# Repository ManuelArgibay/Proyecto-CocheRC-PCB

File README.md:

# Proyecto MiSE — Custom PCB

View this project on [CADLAB.io](https://cadlab.io/project/30101).

PCB diseñada para la asignatura de Microcontroladores i Sistemes Empotrats (MiSE) de la Universitat de Barcelona. El diseño fue realizado íntegramente en KiCad, incluyendo esquemático, layout y exportación de Gerbers.

## Hardware

| Componente | Descripción |
|---|---|
| MSP430FR2355TPT | Microcontrolador TI MSP430, 48-pin QFP, bajo consumo |
| LMV324 | Amplificador operacional cuádruple (acondicionamiento de señal) |
| THB001P | Switch codificador (C&K Components, 14 pines) |
| LCD 2×16 I2C | Display alfanumérico con interfaz I2C (Midas) |
| LDR | Fotorresistencia para detección de luz |
| WIFI | Módulo de conectividad inalámbrica |
| Crystal | Oscilador de cristal externo |
| Pasivos SMD | Resistencias y condensadores en encapsulado 0805 |

## Estructura del repositorio
├── PCB_MiSE.kicad_pcb       # Layout de la PCB
├── PCB_MiSE.kicad_sch       # Esquemático
├── PCB_MiSE.kicad_pro       # Archivo de proyecto KiCad
├── Gerbers/                  # Archivos de fabricación
├── Componentes/
│   └── MiSE.pretty/         # Librería de footprints personalizada
└── PCB_MiSE-backups/        # Backups automáticos de KiCad

## Fabricación

Los archivos Gerber listos para enviar a fabricar están en la carpeta `Gerbers/`. El diseño es una PCB de 2 capas con componentes SMD (0805) y through-hole.

## Herramientas

- [KiCad](https://www.kicad.org/) 8.x
- [CADLAB.io](https://cadlab.io) — revisión visual de cambios en el PCB

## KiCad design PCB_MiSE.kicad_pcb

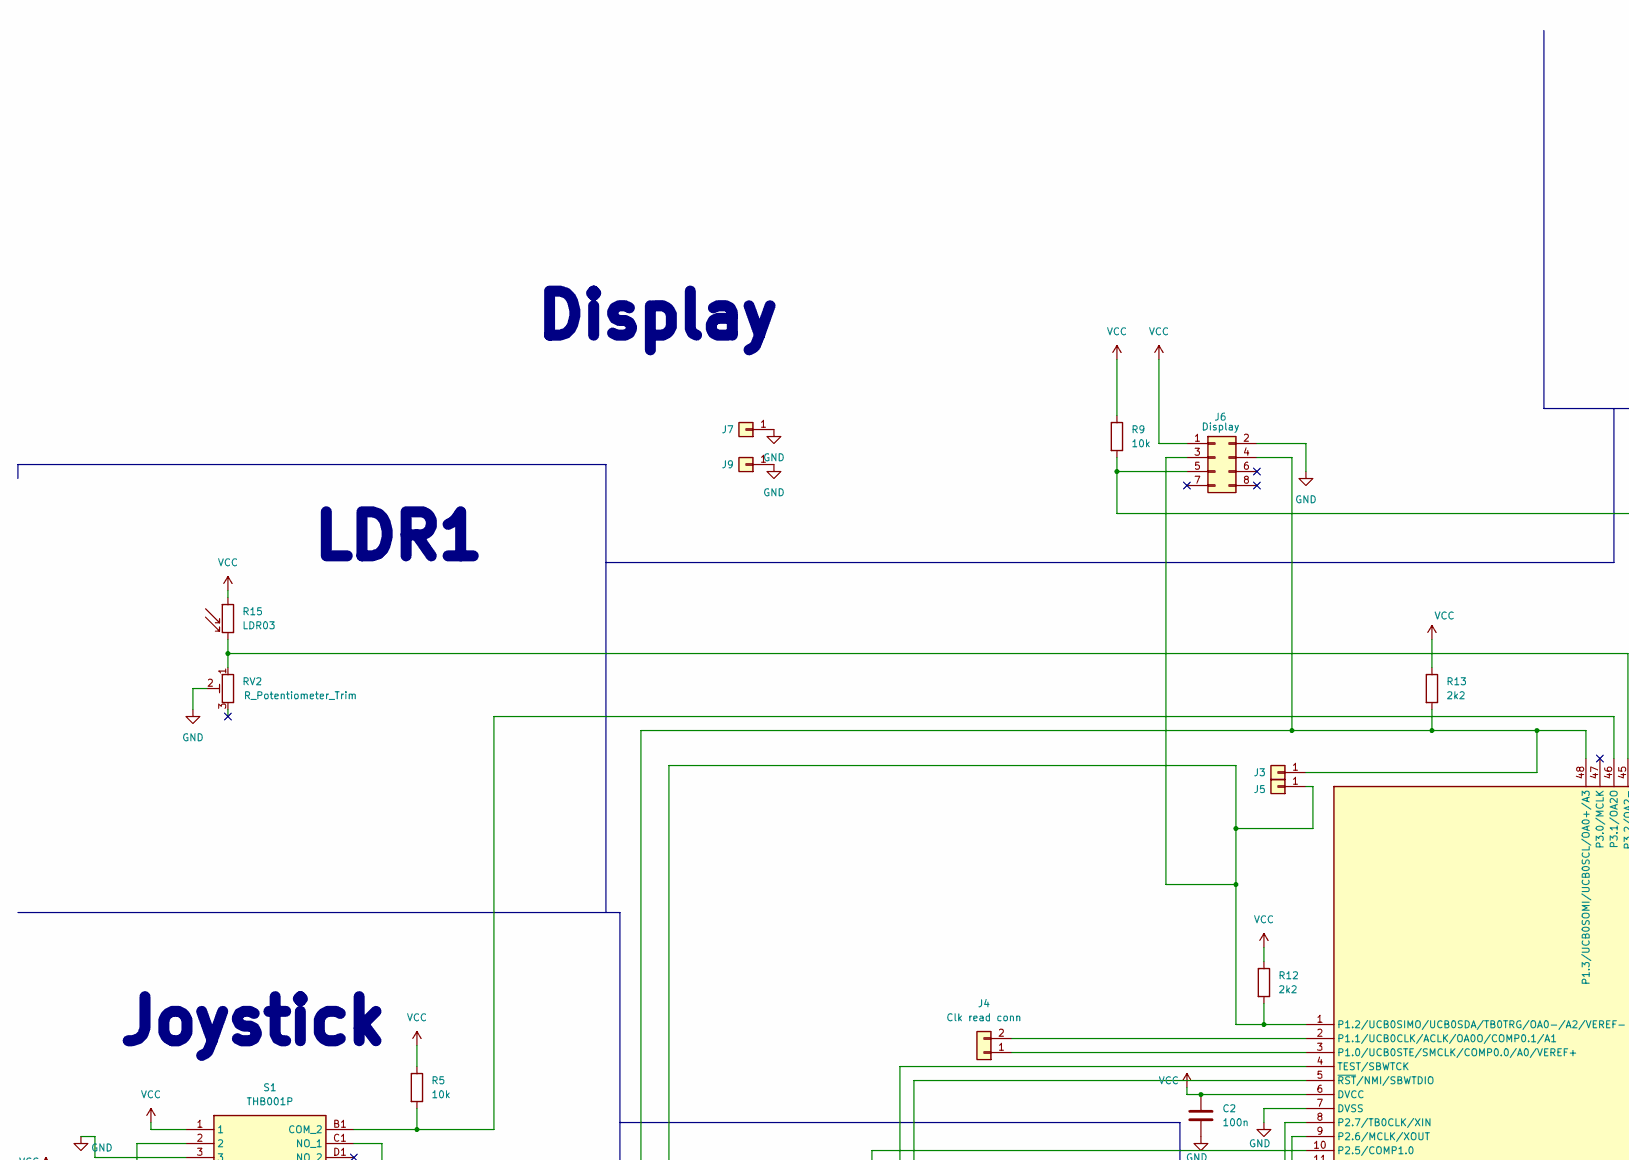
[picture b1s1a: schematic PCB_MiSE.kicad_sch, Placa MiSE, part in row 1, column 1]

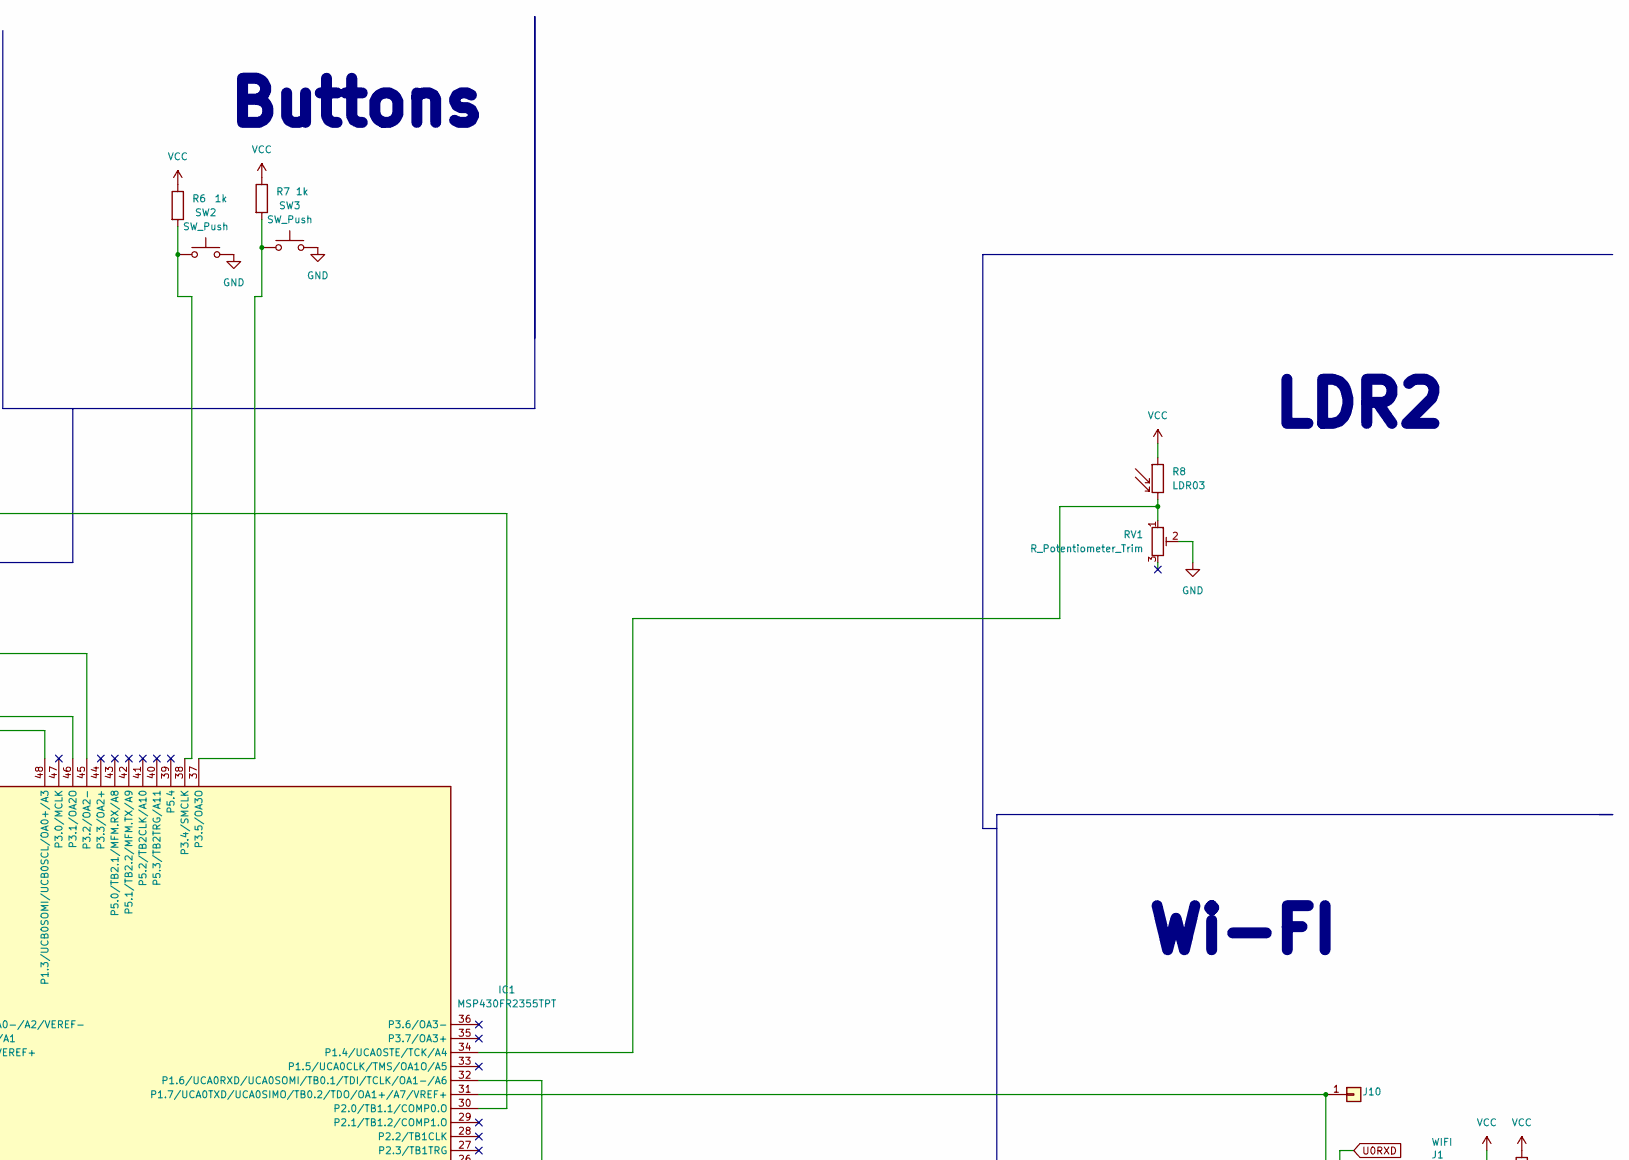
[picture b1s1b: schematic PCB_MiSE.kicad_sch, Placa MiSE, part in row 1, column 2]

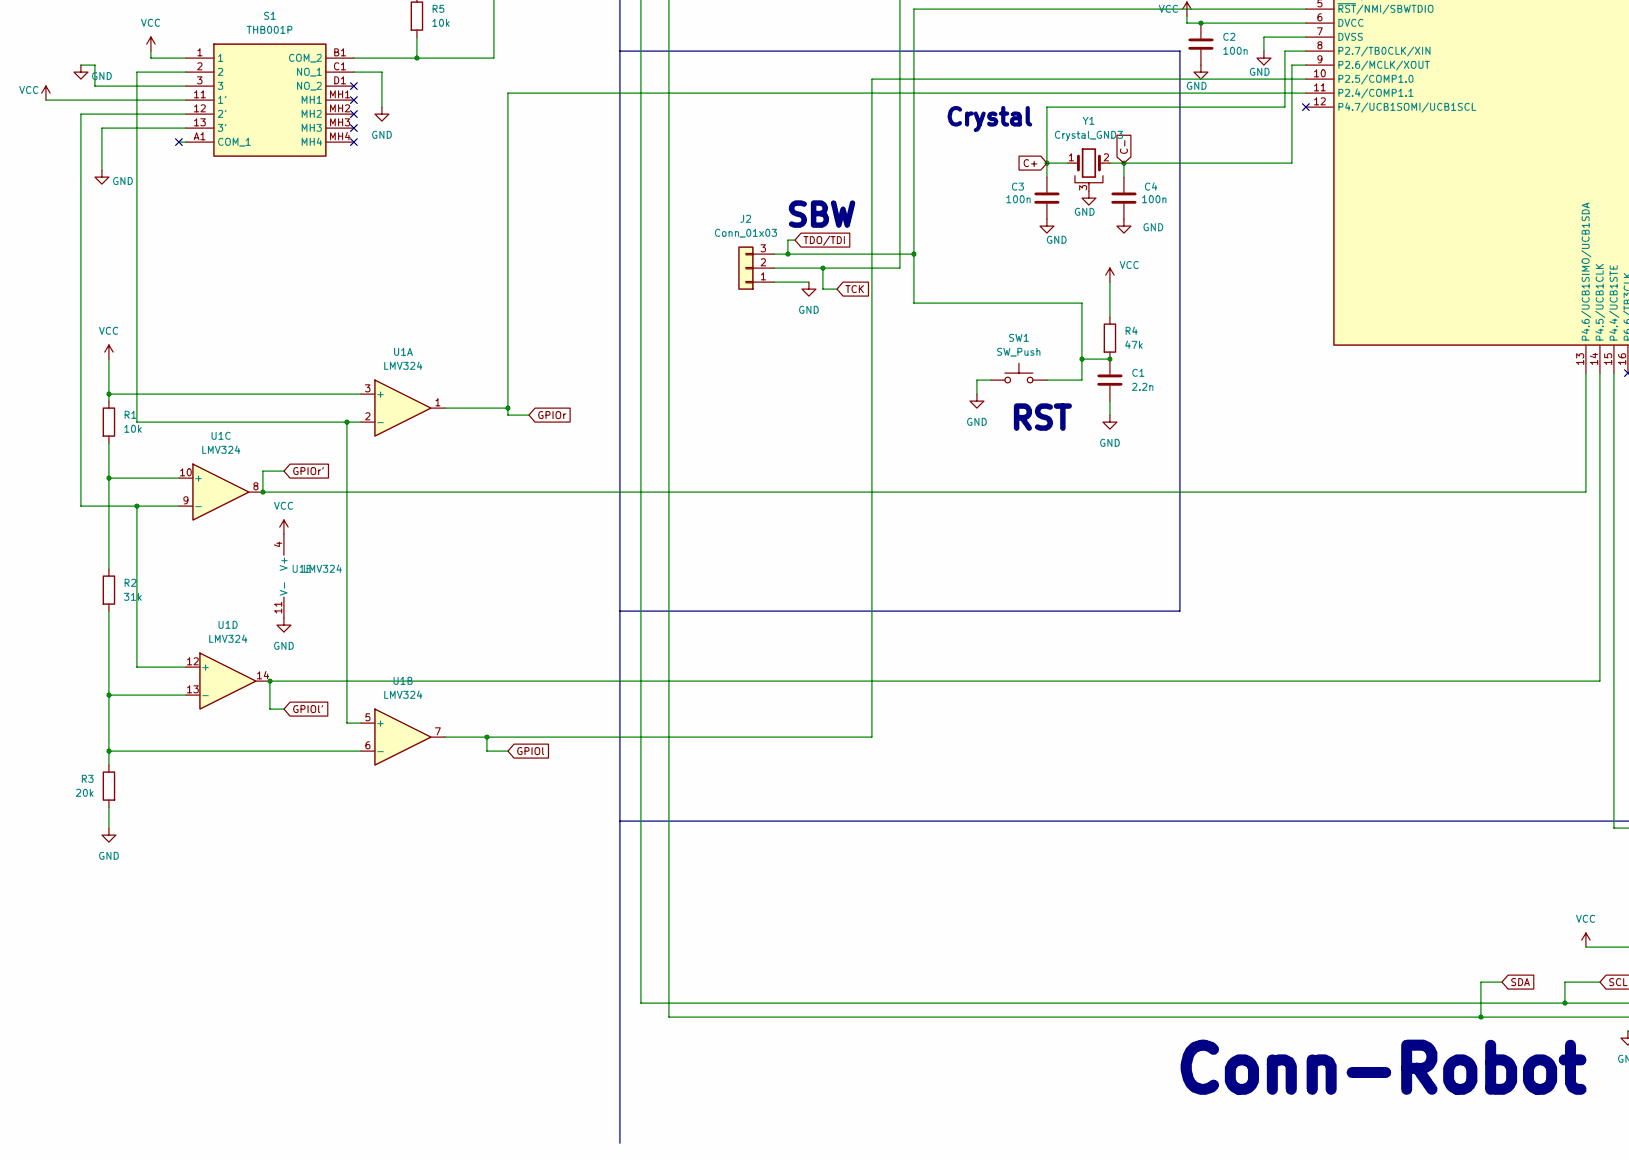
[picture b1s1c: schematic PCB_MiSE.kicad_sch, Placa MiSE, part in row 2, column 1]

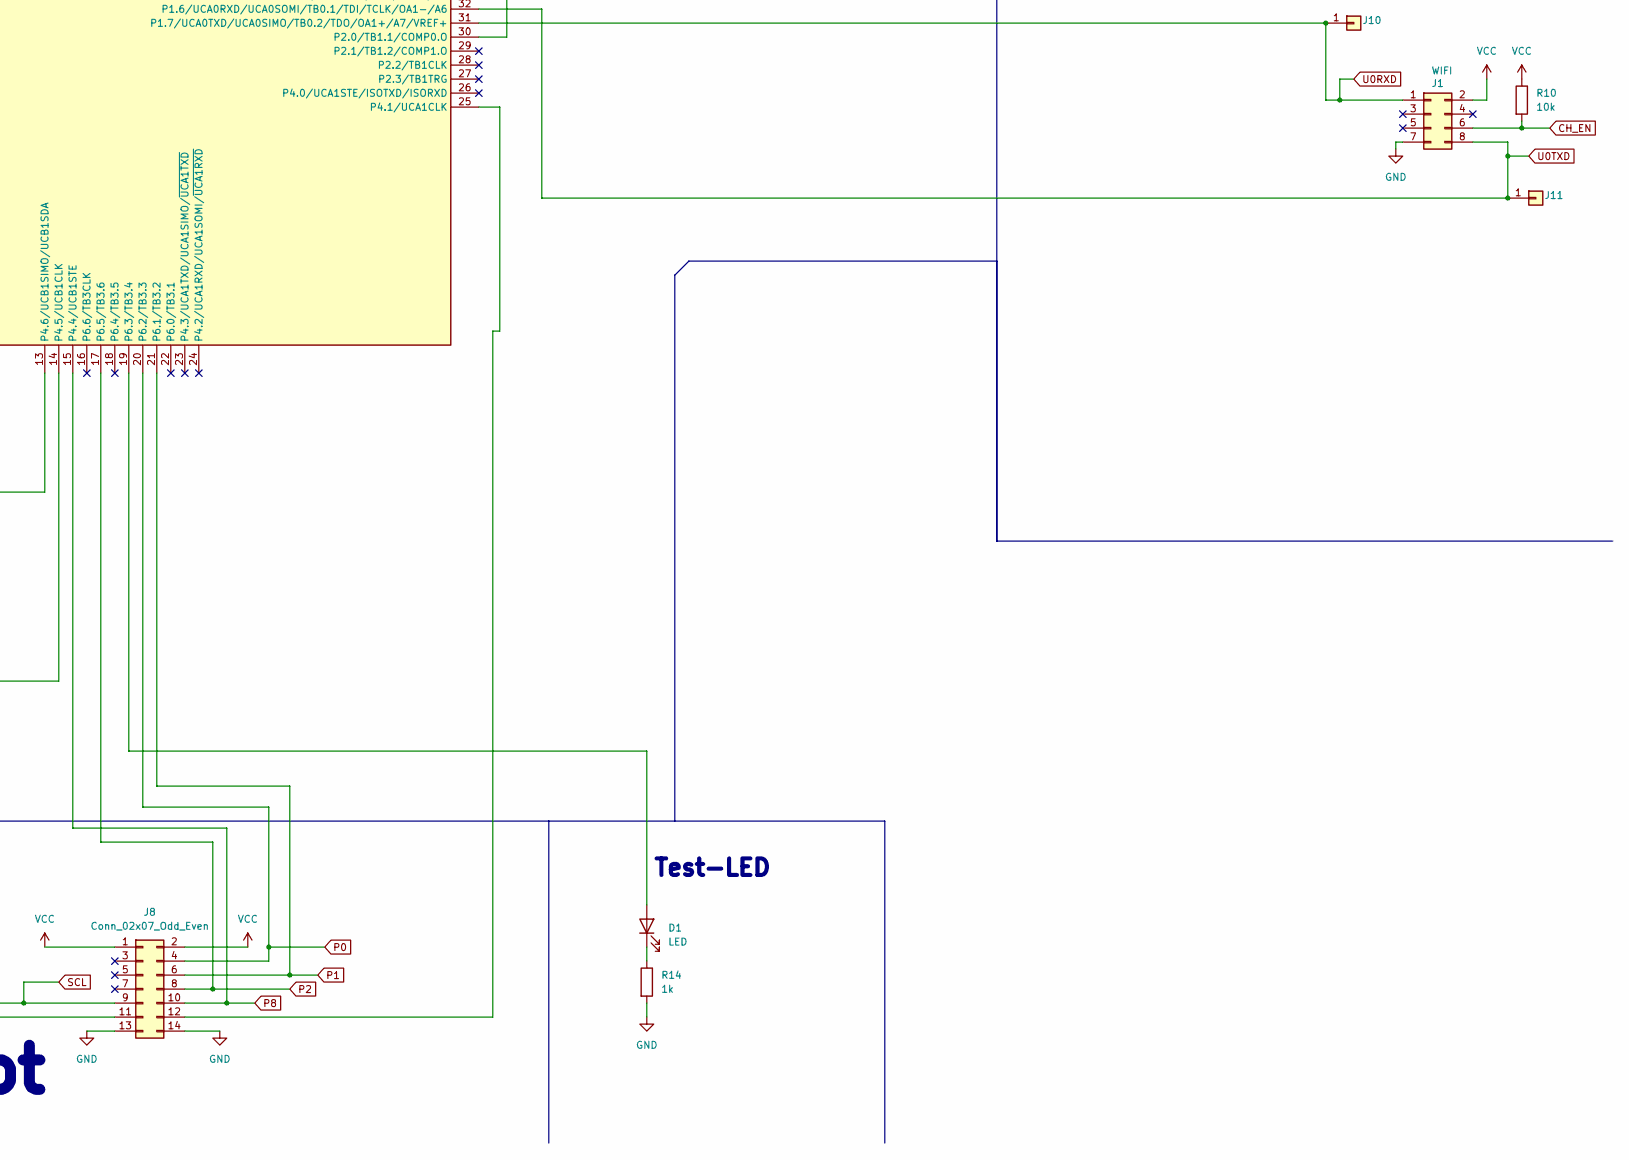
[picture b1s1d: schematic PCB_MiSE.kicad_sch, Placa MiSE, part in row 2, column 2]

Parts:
C1: 2.2n; C_0805_2012Metric_Pad1.18x1.45mm_HandSolder
C2, C3, C4: 100n; C_0805_2012Metric_Pad1.18x1.45mm_HandSolder
D1: LED; LED_0805_2012Metric_Pad1.15x1.40mm_HandSolder
IC1: MSP430FR2355TPT; QFP50P900X900X160-48N; Mouser Part Number 595-MSP430FR2355TPT
J1: WIFI; PinHeader_2x04_P2.54mm_Vertical
J2: Conn_01x03; PinHeader_1x03_P2.54mm_Vertical
J3, J5, J7, J9, J10, J11: Conn_01x01; PinHeader_1x01_P2.54mm_Vertical
J4: Clk read conn; PinHeader_1x02_P2.54mm_Vertical
J6: Display; LCD_2x16_I2C(Midas)
J8: Conn_02x07_Odd_Even; conn_DFrobot
R1, R5, R9, R10: 10k; R_0805_2012Metric_Pad1.20x1.40mm_HandSolder
R2: 31k; R_0805_2012Metric_Pad1.20x1.40mm_HandSolder
R3: 20k; R_0805_2012Metric_Pad1.20x1.40mm_HandSolder
R4: 47k; R_0805_2012Metric_Pad1.20x1.40mm_HandSolder
R6, R7, R14: 1k; R_0805_2012Metric_Pad1.20x1.40mm_HandSolder
R8, R15: LDR03; PinHeader_1x02_P2.54mm_Horizontal
R12, R13: 2k2; R_0805_2012Metric_Pad1.20x1.40mm_HandSolder
RV1, RV2: R_Potentiometer_Trim; Trimmer_MiSE
S1: THB001P; Mouser Part Number 611-THB001P
SW1, SW2, SW3: SW_Push; SW_PUSH_6mm
U1: LMV324; SOIC-14_3.9x8.7mm_P1.27mm
Y1: Crystal_GND3; Crystal_DS26_D2.0mm_L6.0mm_Horizontal_1EP_style1

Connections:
C+: C3.1, IC1.8 (P2.7/TB0CLK/XIN), Y1.1
C-: C4.1, IC1.9 (P2.6/MCLK/XOUT), Y1.2
CH_EN: J1.6, R10.2
GND: C1.2, C2.2, C3.2, C4.2, IC1.7 (DVSS), J1.7, J2.1, J6.2, J7.1, J8.13, J8.14, J9.1, R3.2, R14.2, RV1.2, RV2.2, S1.3, S1.13 (3'), S1.C1 (NO_1), SW1.1, SW2.2, SW3.2, U1.11 (V-), Y1.3
GPIOl: IC1.10 (P2.5/COMP1.0), U1.7
GPIOl': IC1.14 (P4.5/UCB1CLK), U1.14
GPIOr: IC1.11 (P2.4/COMP1.1), U1.1
GPIOr': IC1.13 (P4.6/UCB1SIMO/UCB1SDA), U1.8
unnamed: D1.2 (A), IC1.19 (P6.3/TB3.4)
unnamed: D1.1 (K), R14.1
unnamed: IC1.3 (P1.0/UCB0STE/SMCLK/COMP0.0/A0/VEREF+), J4.1
unnamed: IC1.2 (P1.1/UCB0CLK/ACLK/OA0O/COMP0.1/A1), J4.2
unnamed: IC1.34 (P1.4/UCA0STE/TCK/A4), R8.2, RV1.1
unnamed: IC1.30 (P2.0/TB1.1/COMP0.O), J6.5, R9.2
unnamed: IC1.46 (P3.1/OA2O), R5.2, S1.B1 (COM_2)
unnamed: IC1.45 (P3.2/OA2-), R15.2, RV2.1
unnamed: IC1.38 (P3.4/SMCLK), R6.2, SW2.1
unnamed: IC1.37 (P3.5/OA3O), R7.2, SW3.1
unnamed: IC1.25 (P4.1/UCA1CLK), J8.12
unnamed: S1.12 (2'), U1.9 (-), U1.12 (+)
unnamed: S1.2, U1.2 (-), U1.5 (+)
unnamed: R2.2, R3.1, U1.6 (-), U1.13 (-)
unnamed: R1.2, R2.1, U1.10 (+)
P0: IC1.20 (P6.2/TB3.3), J8.4
P1: IC1.21 (P6.1/TB3.2), J8.6
P2: IC1.17 (P6.5/TB3.6), J8.8
P8: IC1.15 (P4.4/UCB1STE), J8.10
SCL: IC1.48 (P1.3/UCB0SOMI/UCB0SCL/OA0+/A3), J3.1, J6.4, J8.9, R13.2
SDA: IC1.1 (P1.2/UCB0SIMO/UCB0SDA/TB0TRG/OA0-/A2/VE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), J5.1, J6.3, J8.11, R12.2
TCK: IC1.4 (TEST/SBWTCK), J2.2
TDO/TDI: C1.1, IC1.5 (~RST/NMI/SBWTDIO), J2.3, R4.2, SW1.2
U0RXD: IC1.31 (P1.7/UCA0TXD/UCA0SIMO/TB0.2/TDO/OA1+/A7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), J1.1, J10.1
U0TXD: IC1.32 (P1.6/UCA0RXD/UCA0SOMI/TB0.1/TDI/TCLK/OA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), J1.8, J11.1
VCC: C2.1, IC1.6 (DVCC), J1.2, J6.1, J8.1, J8.2, R1.1, R4.1, R5.1, R6.1, R7.1, R8.1, R9.1, R10.1, R12.1, R13.1, R15.1, S1.1, S1.11 (1'), U1.3 (+), U1.4 (V+)

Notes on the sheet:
SBW
Buttons
LDR2
Wi-FI
RST
Conn-Robot
LDR1
Display
Crystal
Joystick
Test-LED

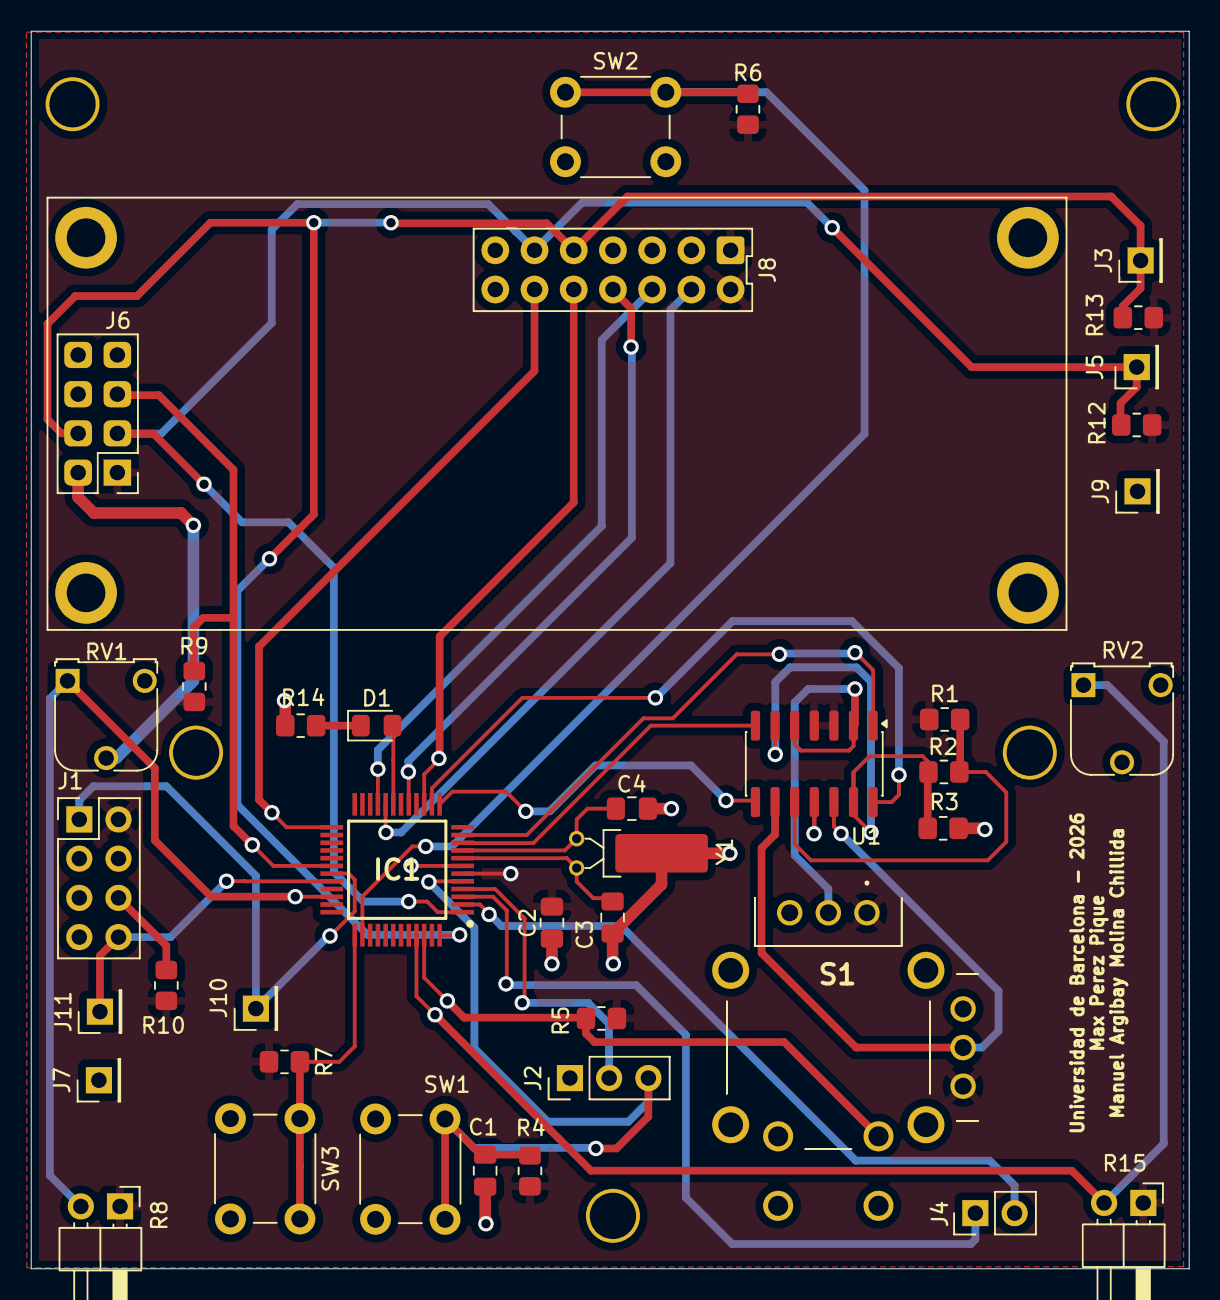
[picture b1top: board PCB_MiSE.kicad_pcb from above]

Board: 2 copper layers, 75.0 x 80.2 mm, 39 parts (0 on the bottom side), 34 nets.

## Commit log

2026-06-12 Primer commit
2026-06-12 Eliminar archivos autogenerados de KiCAD
2026-06-12 Armo el README
